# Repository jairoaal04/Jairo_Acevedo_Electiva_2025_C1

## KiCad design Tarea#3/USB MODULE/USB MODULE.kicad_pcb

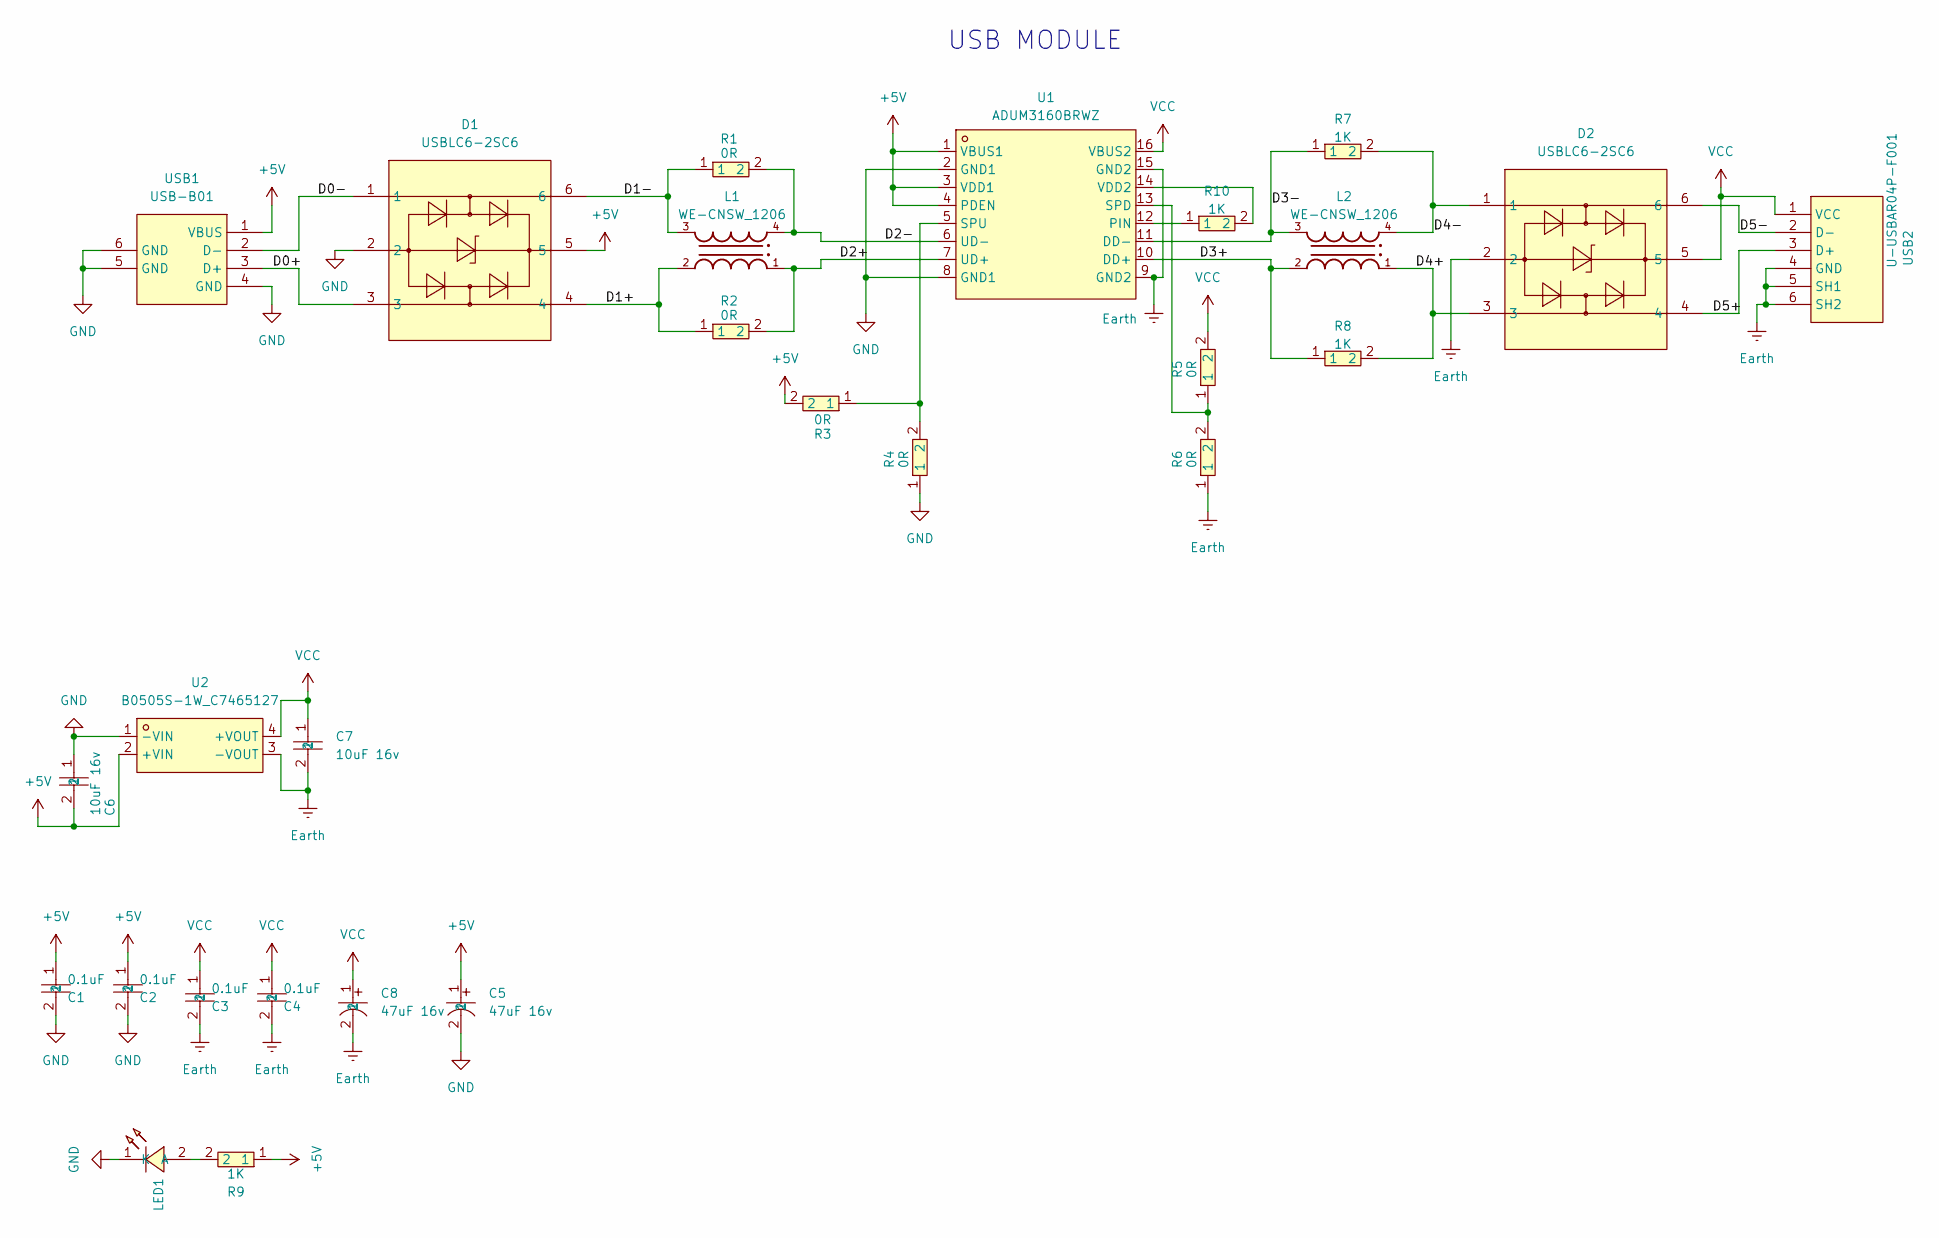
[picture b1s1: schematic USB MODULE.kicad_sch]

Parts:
C1, C2, C3, C4: 0.1uF; C0603; LCSC Part C66501
C5, C8: 47uF 16v; CAP-SMD_BD5.0-L5.3-W5.3-LS6.3-FD; LCSC Part C72515
C6, C7: 10uF 16v; C0805; LCSC Part C1713
D1, D2: USBLC6-2SC6; SOT-23-6_L2.9-W1.6-P0.95-LS2.8-BL; LCSC Part C7519
L1, L2: WE-CNSW_1206; WE-CNSW_1206_WE-CNSW_1206
LED1: XL-1608SURC-06; LED0603-RD_RED; LCSC Part C965799
R1, R2, R3, R4, R5, R6: 0R; R0603; LCSC Part C95177
R7, R8, R9, R10: 1K; R0603; LCSC Part C22548
U1: ADUM3160BRWZ; WSOIC-16_L10.3-W7.5-P1.27-LS10.3-BL; LCSC Part C108501
U2: B0505S-1W_C7465127; PWRM-TH_B0505S-1W; LCSC Part C7465127
USB1: USB-B01; USB-B-TH_USB-B01; LCSC Part C498173
USB2: U-USBAR04P-F001; USB-A-TH_USB-302-T; LCSC Part C386736

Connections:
+5V: C1.1, C2.1, C5.1, C6.2, D1.5, R3.2, R9.1, U1.1 (VBUS1), U1.3 (VDD1), U1.4 (PDEN), U2.2 (+VIN), USB1.1 (VBUS)
/D0+: D1.3, USB1.3 (D+)
/D0-: D1.1, USB1.2 (D-)
/D1+: D1.4, L1.2, R2.1
/D1-: D1.6, L1.3, R1.1
/D2+: L1.1, R2.2, U1.7 (UD+)
/D2-: L1.4, R1.2, U1.6 (UD-)
/D3+: L2.2, R8.1, U1.10 (DD+)
/D3-: L2.3, R7.1, U1.11 (DD-)
/D4+: D2.3, L2.1, R8.2
/D4-: D2.1, L2.4, R7.2
/D5+: D2.4, USB2.3 (D+)
/D5-: D2.6, USB2.2 (D-)
Earth: C3.2, C4.2, C7.2, C8.2, D2.2, R6.1, U1.9 (GND2), U1.15 (GND2), U2.3 (-VOUT), USB2.4 (GND), USB2.5 (SH1), USB2.6 (SH2)
GND: C1.2, C2.2, C5.2, C6.1, D1.2, LED1.1 (K), R4.1, U1.2 (GND1), U1.8 (GND1), U2.1 (-VIN), USB1.4 (GND), USB1.5 (GND), USB1.6 (GND)
unnamed: LED1.2 (A), R9.2
unnamed: R10.1, U1.12 (PIN)
unnamed: R5.1, R6.2, U1.13 (SPD)
unnamed: R3.1, R4.2, U1.5 (SPU)
unnamed: R10.2, U1.14 (VDD2)
VCC: C3.1, C4.1, C7.1, C8.1, D2.5, R5.2, U1.16 (VBUS2), U2.4 (+VOUT), USB2.1 (VCC)

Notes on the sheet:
USB MODULE

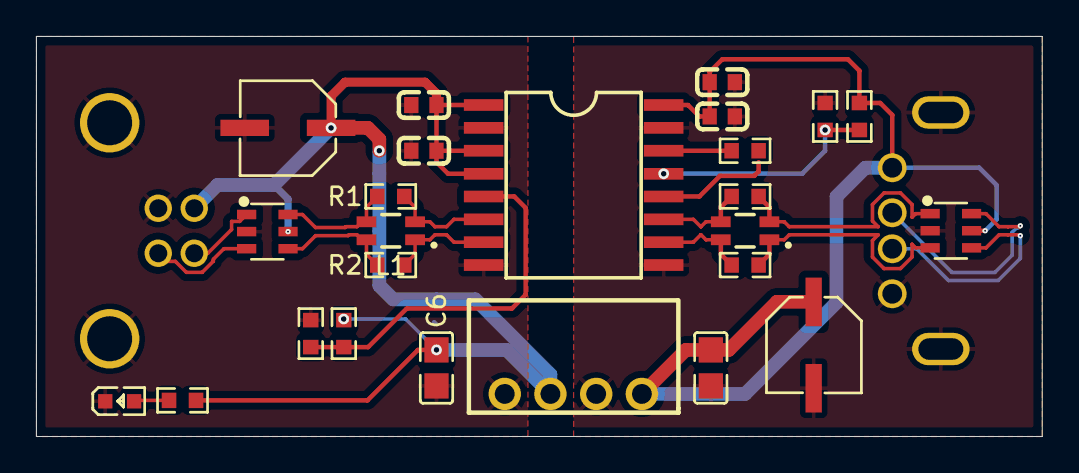
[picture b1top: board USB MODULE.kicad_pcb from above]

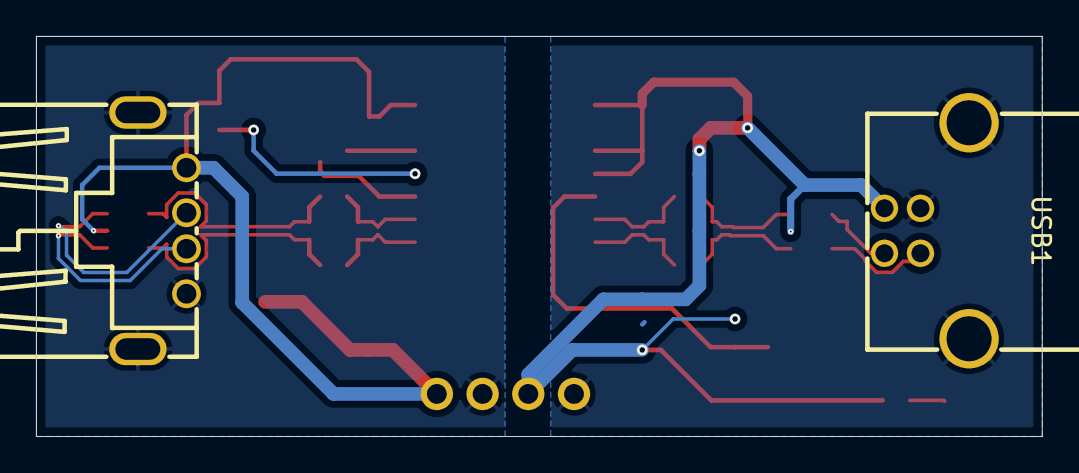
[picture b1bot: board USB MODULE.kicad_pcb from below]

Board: 2 copper layers, 55.9 x 22.2 mm, 27 parts (2 on the bottom side), 21 nets.

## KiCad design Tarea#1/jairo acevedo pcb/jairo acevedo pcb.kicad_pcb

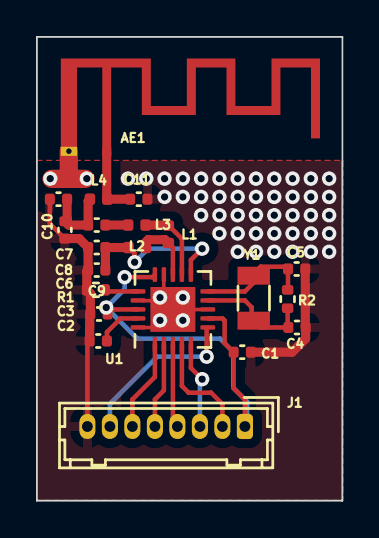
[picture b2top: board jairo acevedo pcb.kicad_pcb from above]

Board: 2 copper layers, 17.0 x 25.8 mm, 21 parts (0 on the bottom side), 18 nets.

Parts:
AE1: Antenna; Texas_SWRA117D_2.4GHz_Right
C1: 1nF; C_0402_1005Metric
C2: 33nF; C_0402_1005Metric
C3: 10nF; C_0402_1005Metric
C4, C5: 22pF; C_0402_1005Metric
C6: 2.2nF; C_0402_1005Metric
C7: 1.5pF; C_0402_1005Metric
C8: 1.0pF; C_0402_1005Metric
C9: 4.7pF; C_0402_1005Metric
C10, C11: Cx; C_0402_1005Metric
J1: Conn_01x08_Pin; Hirose_DF13-08P-1.25DSA_1x08_P1.25mm_Vertical
L1: 8.2nH; L_0402_1005Metric
L2: 2.7nH; L_0402_1005Metric
L3: 3.9nH; L_0402_1005Metric
L4: Lx; L_0402_1005Metric
R1: 22k; R_0402_1005Metric
R2: 10M; R_0402_1005Metric
U1: NRF24L01; QFN-20-1EP_4x4mm_P0.5mm_EP2.5x2.5mm
Y1: 16MHz; Crystal_SMD_3215-2Pin_3.2x1.5mm

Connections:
GND: C1.2, C2.2, C3.2, C4.2, C5.2, C6.2, C8.2, C9.2, C10.2, C11.2, J1.8, R1.2, U1.8 (VSS), U1.14 (VSS), U1.17 (VSS), U1.20 (VSS)
unnamed: AE1.1 (A), C11.1, L4.2
unnamed: C7.1, L2.2
unnamed: C7.2, C8.1, C10.1, L4.1
unnamed: J1.2, U1.4 (MOSI)
unnamed: J1.3, U1.5 (MISO)
unnamed: J1.4, U1.3 (SCK)
unnamed: J1.5, U1.2 (CSN)
unnamed: J1.6, U1.1 (CE)
unnamed: J1.7, U1.6 (IRQ)
unnamed: L1.1, L2.1, U1.12 (ANT1)
unnamed: L1.2, L3.2, U1.13 (ANT2)
unnamed: C2.1, U1.19 (DVDD)
unnamed: R1.1, U1.16 (IREF)
unnamed: C6.1, C9.1, L3.1, U1.11 (VDD_PA)
unnamed: C5.1, R2.2, U1.10 (XC1), Y1.2
unnamed: C4.1, R2.1, U1.9 (XC2), Y1.1
VDD: C1.1, C3.1, J1.1, U1.7 (VDD), U1.15 (VDD), U1.18 (VDD)

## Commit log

2025-01-24 Create .algo
    Es para crear la carpeta.
2025-02-13 prueba
    prueba
2025-04-26 Update
    Tarea final, PLC en Solidedge y Freecad
